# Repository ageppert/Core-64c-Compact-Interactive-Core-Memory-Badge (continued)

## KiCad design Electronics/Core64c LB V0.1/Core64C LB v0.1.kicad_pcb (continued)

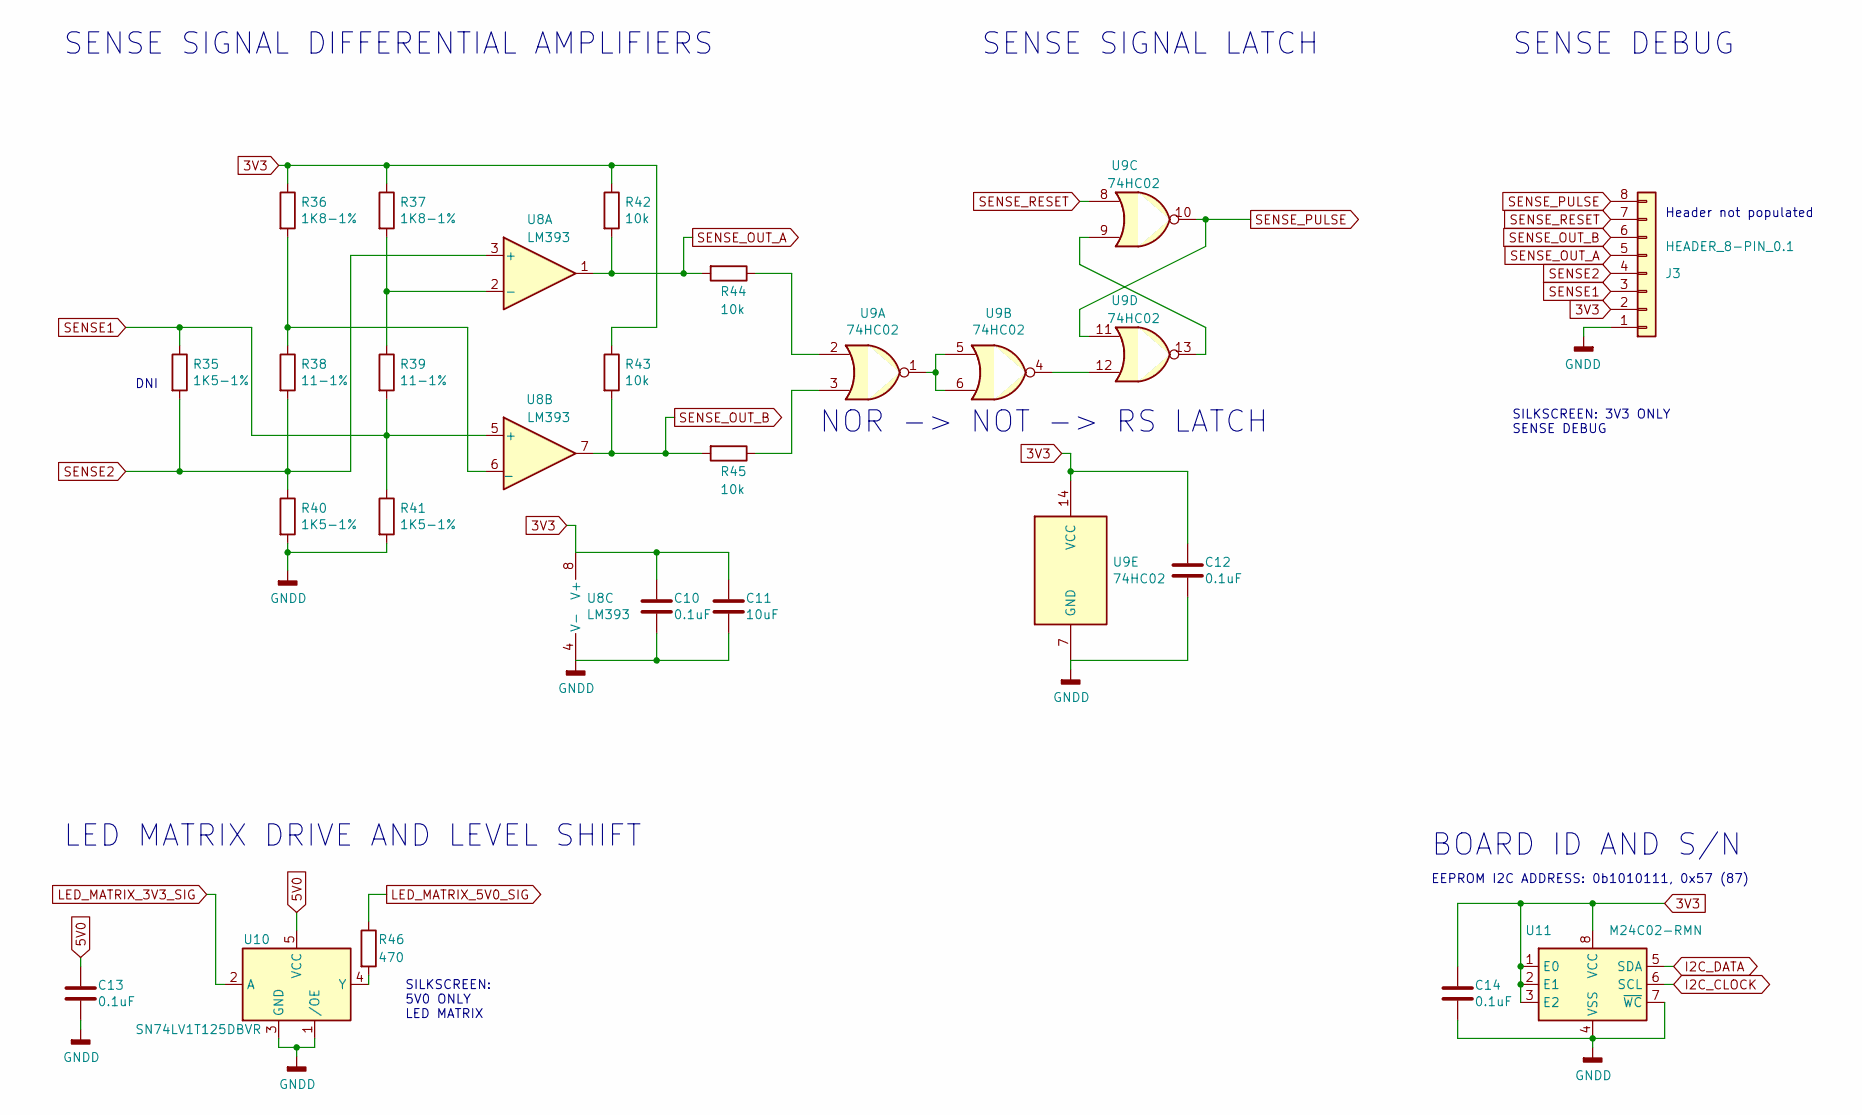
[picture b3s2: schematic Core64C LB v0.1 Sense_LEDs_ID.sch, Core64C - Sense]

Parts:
C10, C12, C13, C14: 0.1uF; C_0805_2012Metric
C11: 10uF; C_0805_2012Metric
J3: HEADER_8-PIN_0.1; PinSocket_1x08_P2.54mm_Vertical
R35, R40, R41: 1K5-1%; R_0805_2012Metric
R36, R37: 1K8-1%; R_0805_2012Metric
R38, R39: 11-1%; R_0805_2012Metric
R42, R43, R44, R45: 10k; R_0805_2012Metric
R46: 470; R_0805_2012Metric
U3, U8: LM393; SOIC-8_W3.9mm
U9: 74HC02; SOIC-14_3.9x8.7mm_P1.27mm
U10: SN74LV1T125DBVR; SOT-23-5; LCSC C473338
U11: M24C02-RMN; SOIC-8_3.9x4.9mm_P1.27mm

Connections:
3V3: C10.1, C11.1, C12.1, C14.1, J3.2, R36.1, R37.1, R42.1, R43.1, U8.8 (V+), U9.14 (VCC), U11.1 (E0), U11.2 (E1), U11.3 (E2), U11.8 (VCC); also elsewhere on the board
5V0: C13.1, U10.5 (VCC); also elsewhere on the board
-BATT: C10.2, C11.2, C12.2, C13.2, C14.2, J3.1, R40.2, R41.2, U8.4 (V-), U9.7 (GND), U10.1 (/OE), U10.3 (GND), U11.4 (VSS), U11.7 (~WC); also elsewhere on the board
I2C_CLOCK: U11.6 (SCL); also elsewhere on the board
I2C_DATA: U11.5 (SDA); also elsewhere on the board
LED_MATRIX_3V3_SIG: U10.2 (A); also elsewhere on the board
LED_MATRIX_5V0_SIG: R46.1; also elsewhere on the board
unnamed: R36.2, R38.1, U8.6 (_)
unnamed: R44.1, U9.2
unnamed: R45.1, U9.3
unnamed: R46.2, U10.4 (Y)
unnamed: U9.1, U9.5, U9.6
unnamed: U9.4, U9.12
unnamed: U9.9, U9.13
SENSE1: J3.3, R35.1, R39.2, R41.1, U8.5 (+); also elsewhere on the board
SENSE_OUT_B: J3.6, R43.2, R45.2, U8.7
SENSE_PULSE: J3.8, U9.10, U9.11; also elsewhere on the board
SENSE_RESET: J3.7, U9.8; also elsewhere on the board

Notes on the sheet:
SENSE SIGNAL DIFFERENTIAL AMPLIFIERS
DNI
SENSE SIGNAL LATCH
SENSE DEBUG
SILKSCREEN: 3V3 ONLY SENSE DEBUG
NOR -> NOT -> RS LATCH
LED MATRIX DRIVE AND LEVEL SHIFT
SILKSCREEN: 5V0 ONLY LED MATRIX
BOARD ID AND S/N
EEPROM I2C ADDRESS: 0b1010111, 0x57 (87)
Header not populated

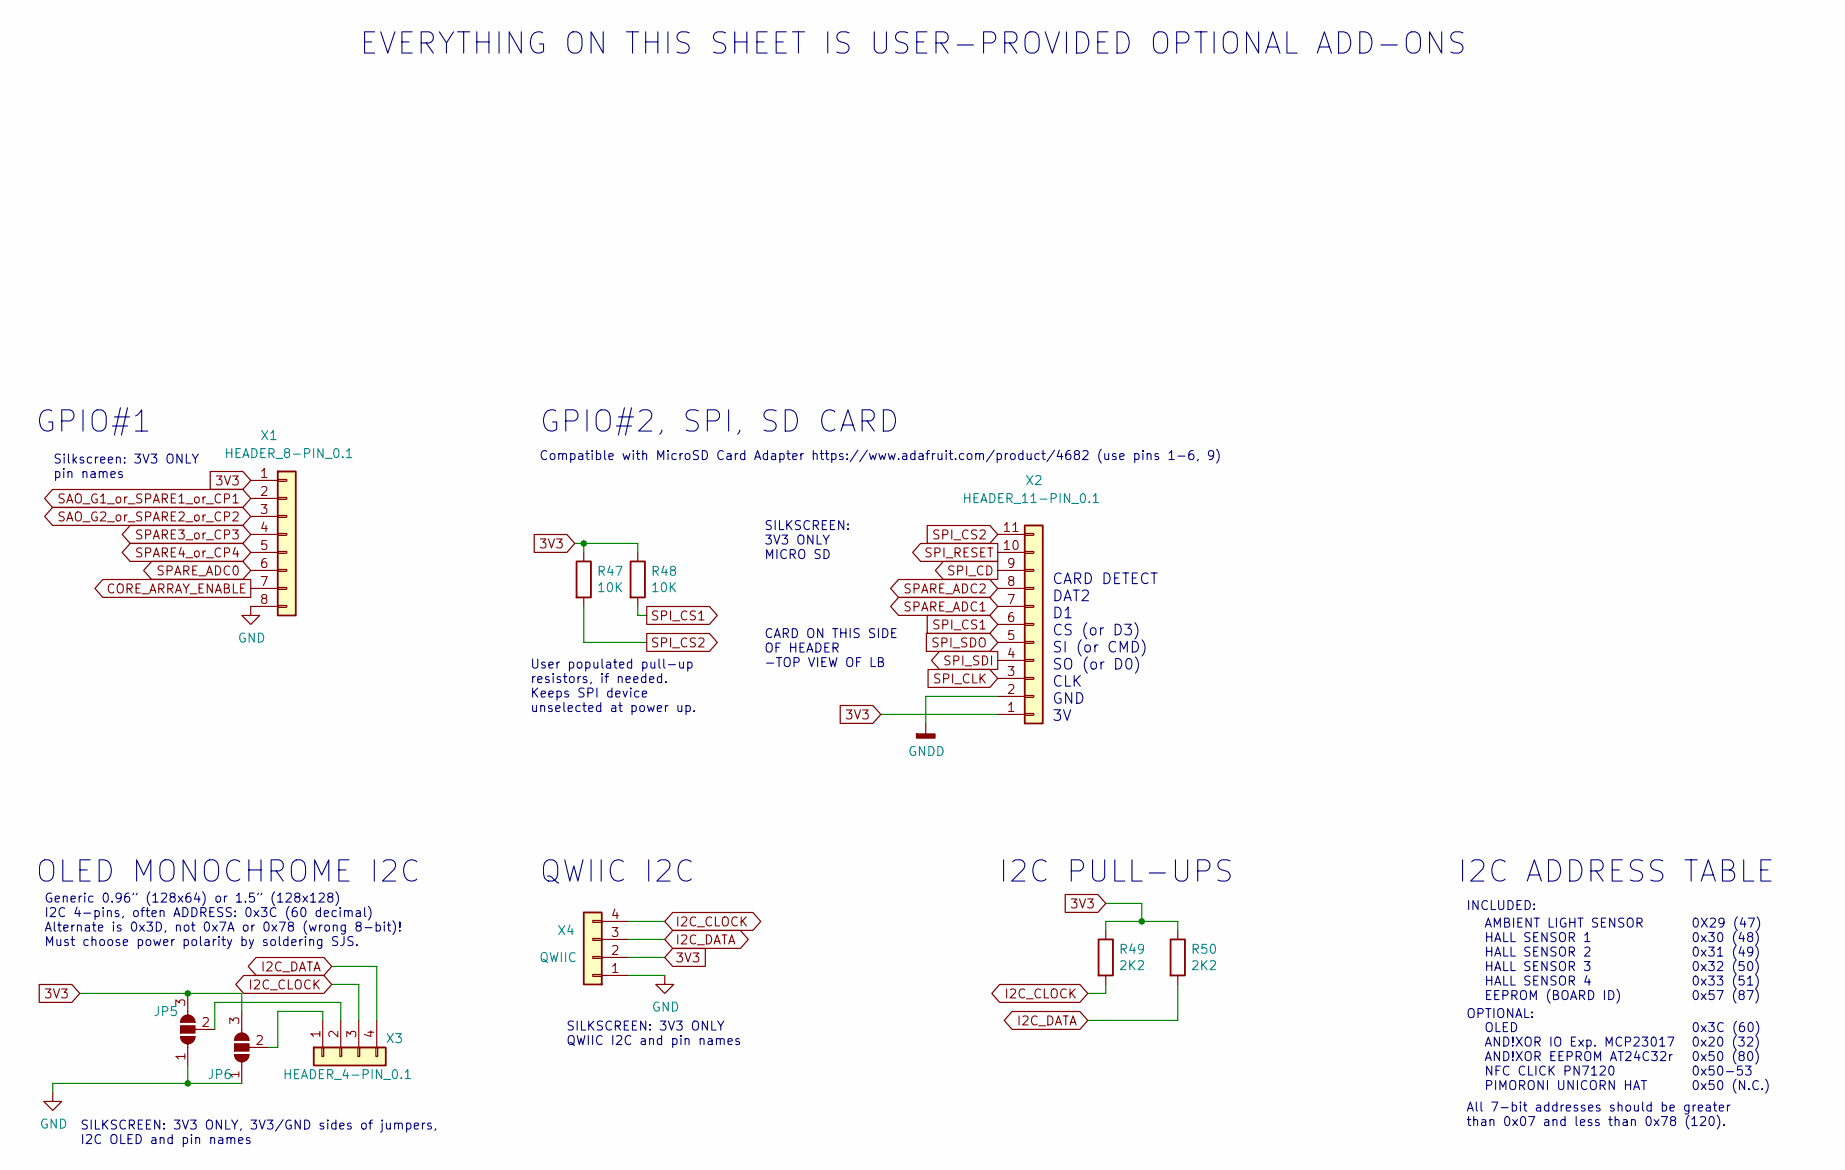
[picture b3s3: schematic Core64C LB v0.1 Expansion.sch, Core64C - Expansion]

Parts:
JP5, JP6: SolderJumper_3_Open; SolderJumper-3_P1.3mm_Open_Pad1.0x1.5mm_NumberLabels
R47, R48: 10K; R_0805_2012Metric
R49, R50: 2K2; R_0805_2012Metric
X1: HEADER_8-PIN_0.1; PinSocket_1x08_P2.54mm_Vertical
X2: HEADER_11-PIN_0.1; PinSocket_1x11_P2.54mm_Vertical
X3: HEADER_4-PIN_0.1; PinSocket_1x04_P2.54mm_Vertical
X4: QWIIC; JST_SH_SM04B-SRSS-TB_1x04-1MP_P1.00mm_Horizontal

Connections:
3V3: JP5.3 (B), JP6.3 (B), R47.1, R48.1, R49.1, R50.1, X1.1, X2.1, X4.2; also elsewhere on the board
3V3_MON: X2.7; also elsewhere on the board
-BATT: JP5.1 (A), JP6.1 (A), X1.8, X2.2, X4.1; also elsewhere on the board
BAT_MON: X1.6; also elsewhere on the board
CORE_ARRAY_ENABLE: X1.7; also elsewhere on the board
CP1_EN: X1.2; also elsewhere on the board
CP2_EN: X1.3; also elsewhere on the board
CP3_EN: X1.4, X2.9; also elsewhere on the board
CP4_EN: X1.5, X2.10; also elsewhere on the board
HS1: X2.4; also elsewhere on the board
HS2: R48.2, X2.6; also elsewhere on the board
HS3: X2.3; also elsewhere on the board
HS4: X2.5; also elsewhere on the board
I2C_CLOCK: R49.2, X3.3, X4.4; also elsewhere on the board
I2C_DATA: R50.2, X3.4, X4.3; also elsewhere on the board
LED_MATRIX_3V3_SIG: R47.2, X2.11; also elsewhere on the board
unnamed: JP5.2 (C), X3.2
unnamed: JP6.2 (C), X3.1
SPARE_ADC2: X2.8; also elsewhere on the board

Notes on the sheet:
OLED MONOCHROME I2C
Generic 0.96” (128x64) or 1.5” (128x128) I2C 4-pins, often ADDRESS: 0x3C (60 decimal) Alternate is 0x3D, not 0x7A or 0x78 (wrong 8-bit)! Must choose power polarity by soldering SJS.
QWIIC I2C
SILKSCREEN: 3V3 ONLY, 3V3/GND sides of jumpers, I2C OLED and pin names
Silkscreen: 3V3 ONLY pin names
GPIO#1
EVERYTHING ON THIS SHEET IS USER-PROVIDED OPTIONAL ADD-ONS
SILKSCREEN: 3V3 ONLY QWIIC I2C and pin names
All 7-bit addresses should be greater than 0x07 and less than 0x78 (120).
AMBIENT LIGHT SENSOR HALL SENSOR 1 HALL SENSOR 2 HALL SENSOR 3 HALL SENSOR 4 EEPROM (BOARD ID)
0X29 (47) 0x30 (48) 0x31 (49) 0x32 (50) 0x33 (51) 0x57 (87)
INCLUDED:
OPTIONAL:
OLED AND!XOR IO Exp. MCP23017 AND!XOR EEPROM AT24C32r NFC CLICK PN7120 PIMORONI UNICORN HAT
0x3C (60) 0x20 (32) 0x50 (80) 0x50-53 0x50 (N.C.)
I2C ADDRESS TABLE
I2C PULL-UPS
GPIO#2, SPI, SD CARD
Compatible with MicroSD Card Adapter https://www.adafruit.com/product/4682 (use pins 1-6, 9)
SILKSCREEN: 3V3 ONLY MICRO SD
CARD ON THIS SIDE OF HEADER -TOP VIEW OF LB
CARD DETECT DAT2 D1 CS (or D3) SI (or CMD) SO (or D0) CLK GND 3V
User populated pull-up resistors, if needed. Keeps SPI device unselected at power up.

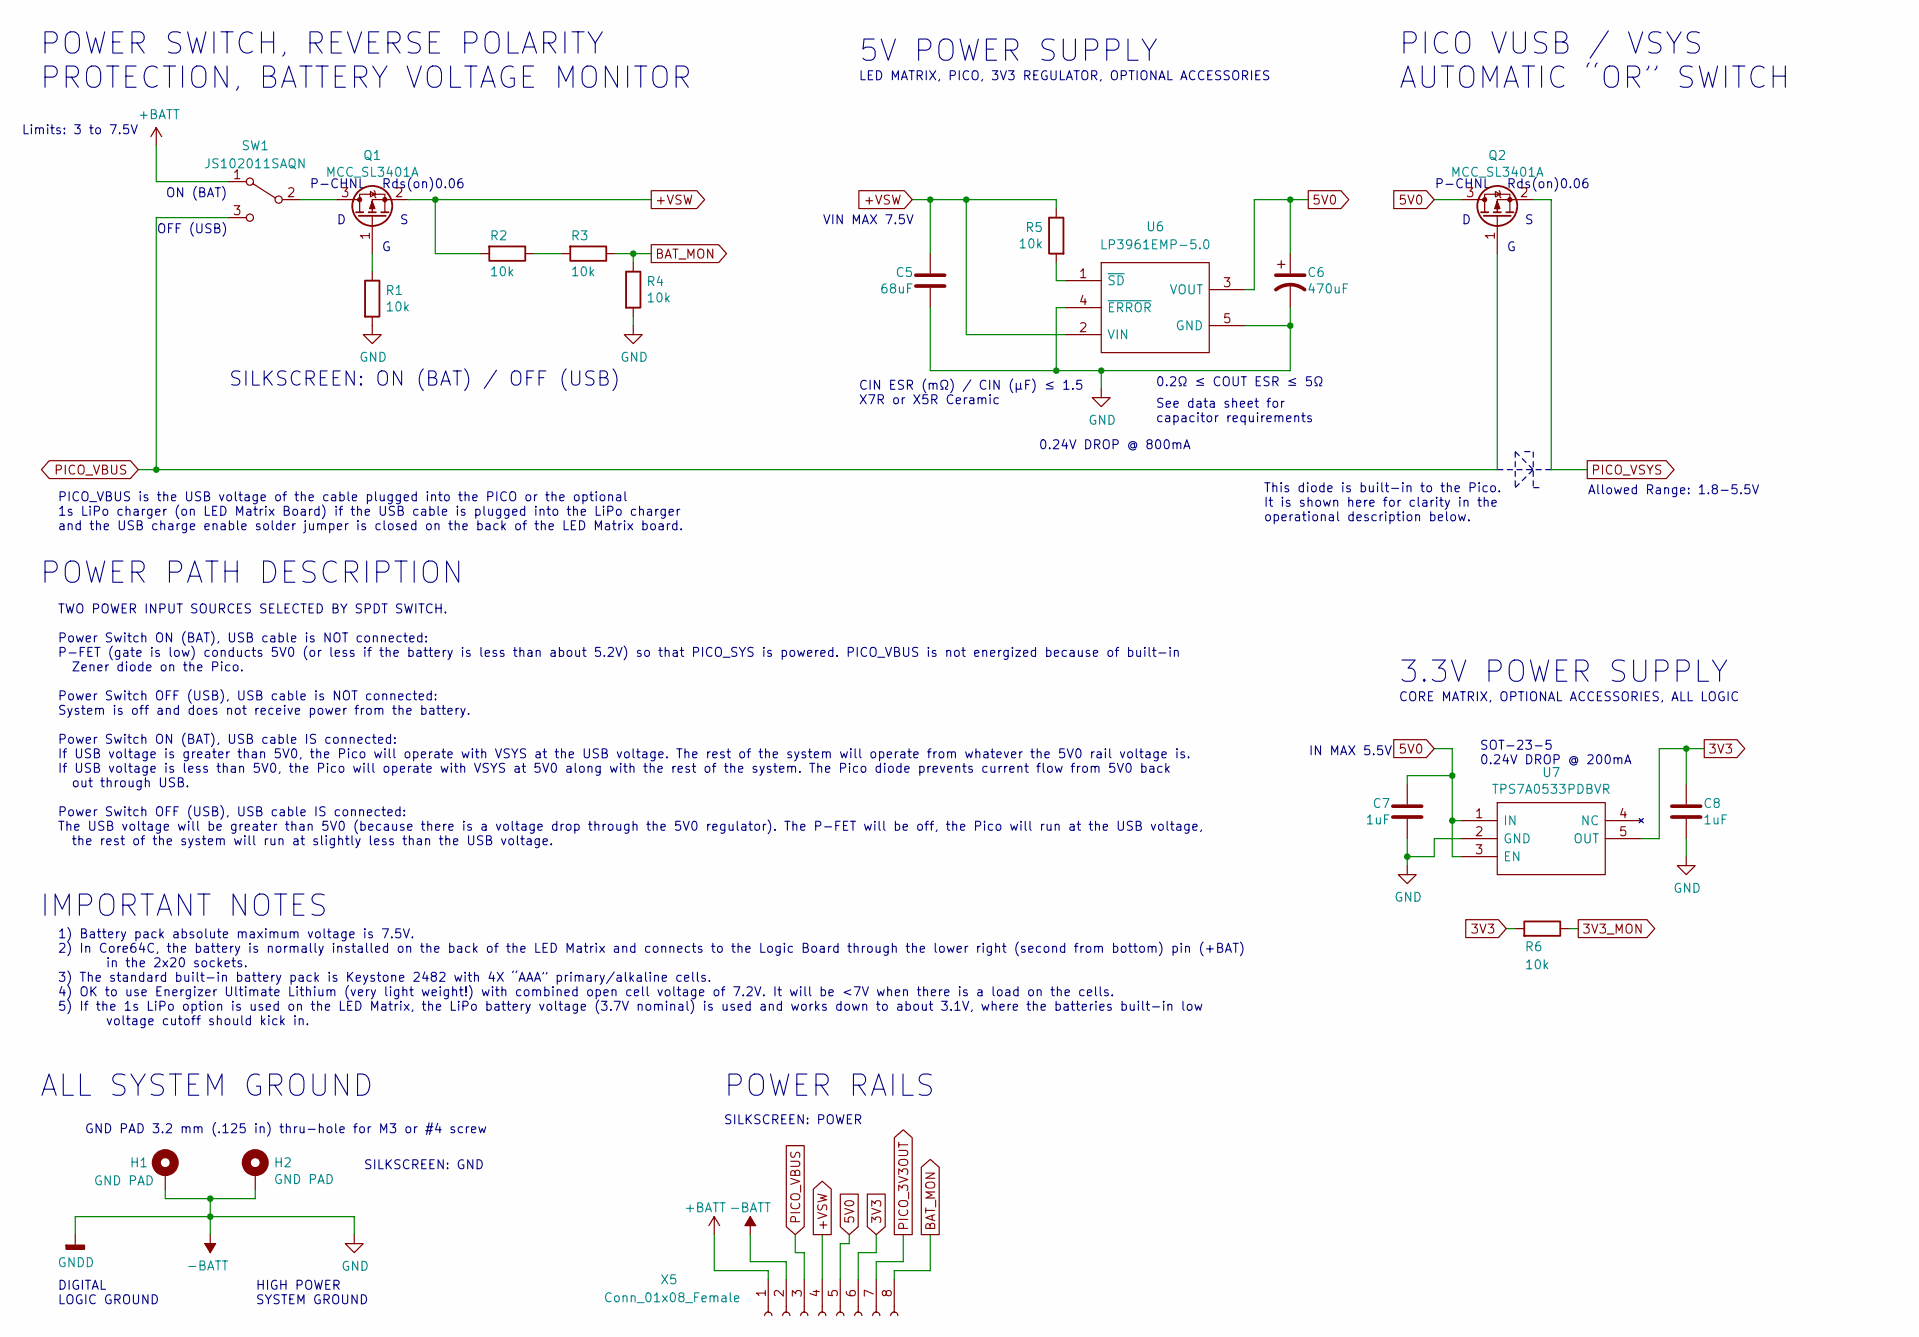
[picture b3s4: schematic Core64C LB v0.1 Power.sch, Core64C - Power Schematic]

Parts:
C5: 68uF; C_1206_3216Metric
C6: 470uF; CP_Elec_6.3x7.7; Digi-Key_PN 565-EMHL100ARA471MHA0GCT-ND
C7, C8: 1uF; C_0805_2012Metric
H1, H2: GND PAD; MountingHole_3.2mm_M3_Pad_Via
Q1, Q2: MCC_SL3401A; SOT-23-3; LCSC C350311
R1, R2, R3, R4, R5, R6: 10k; R_0805_2012Metric
SW1: JS102011SAQN; SW_SPDT_CK-JS102011SAQN_Core64_Recessed
U6: LP3961EMP-5.0; SOT150P696X180-5N; Manufacturer_Part_Number LP3961EMP-5.0; Mouser Part Number 926-LP3961EMP-50
U7: TPS7A0533PDBVR; SOT95P280X145-5N; Manufacturer_Part_Number TPS7A0533PDBVR; Mouser Part Number 595-TPS7A0533PDBVR
X5: Conn_01x08_Female; PinSocket_1x08_P2.54mm_Vertical

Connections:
3V3: C8.1, R6.2, U7.5 (OUT), X5.6; also elsewhere on the board
3V3_MON: R6.1; also elsewhere on the board
5V0: C6.1, C7.1, Q2.3 (D), U6.3 (VOUT), U7.1 (IN), U7.3 (EN), X5.5; also elsewhere on the board
+BATT: SW1.1 (A), X5.1; also elsewhere on the board
+VSW: C5.1, Q1.2 (S), R2.2, R5.1, U6.2 (VIN), X5.4
-BATT: C5.2, C6.2, C7.2, C8.2, H1.1, H2.1, R1.2, R4.2, U6.4 (~ERROR), U6.5 (GND), U7.2 (GND), X5.2; also elsewhere on the board
BAT_MON: R3.1, R4.1, X5.8; also elsewhere on the board
unnamed: Q1.1 (G), R1.1
unnamed: Q1.3 (D), SW1.2 (B)
unnamed: R2.1, R3.2
unnamed: R5.2, U6.1 (~SD)
PICO_3V3OUT: X5.7; also elsewhere on the board
PICO_VBUS: Q2.1 (G), SW1.3 (C), X5.3; also elsewhere on the board
PICO_VSYS: Q2.2 (S); also elsewhere on the board

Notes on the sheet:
CORE MATRIX, OPTIONAL ACCESSORIES, ALL LOGIC
POWER SWITCH, REVERSE POLARITY PROTECTION, BATTERY VOLTAGE MONITOR
3.3V POWER SUPPLY
LED MATRIX, PICO, 3V3 REGULATOR, OPTIONAL ACCESSORIES
ALL SYSTEM GROUND
POWER RAILS
HIGH POWER SYSTEM GROUND
DIGITAL LOGIC GROUND
SILKSCREEN: ON (BAT) / OFF (USB)
5V POWER SUPPLY
P-CHNL
SOT-23-5 0.24V DROP @ 200mA
CIN ESR (mΩ) / CIN (μF) ≤ 1.5 X7R or X5R Ceramic
0.2Ω ≤ COUT ESR ≤ 5Ω
See data sheet for capacitor requirements
GND PAD 3.2 mm (.125 in) thru-hole for M3 or #4 screw
SILKSCREEN: GND
SILKSCREEN: POWER
ON (BAT)
OFF (USB)
Rds(on)0.06
VIN MAX 7.5V
0.24V DROP @ 800mA
IN MAX 5.5V
Allowed Range: 1.8-5.5V
TWO POWER INPUT SOURCES SELECTED BY SPDT SWITCH. Power Switch ON (BAT), USB cable is NOT connected: P-FET (gate is low) conducts 5V0 (or less if the battery is less than about 5.2V) so that PICO_SYS is powered. PICO_VBUS is not energized because of built-in Zener diode on the Pico. Power Switch OFF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
PICO VUSB / VSYS AUTOMATIC “OR” SWITCH
This diode is built-in to the Pico. It is shown here for clarity in the operational description below.
PICO_VBUS is the USB voltage of the cable plugged into the PICO or the optional 1s LiPo charger (on LED Matrix Board) if the USB cable is plugged into the LiPo charger and the USB charge enable solder jumper is closed on the back of the LED Matrix board.
POWER PATH DESCRIPTION
1) Battery pack absolute maximum voltage is 7.5V. 2) In Core64C, the battery is normally installed on the back of the LED Matrix and connects to the Logic Board through the lower right (second from bottom) pin (+BAT) in the 2x20 sockets. 3) The standard built-in battery pack is Keystone 2482 with 4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
IMPORTANT NOTES
Limits: 3 to 7.5V

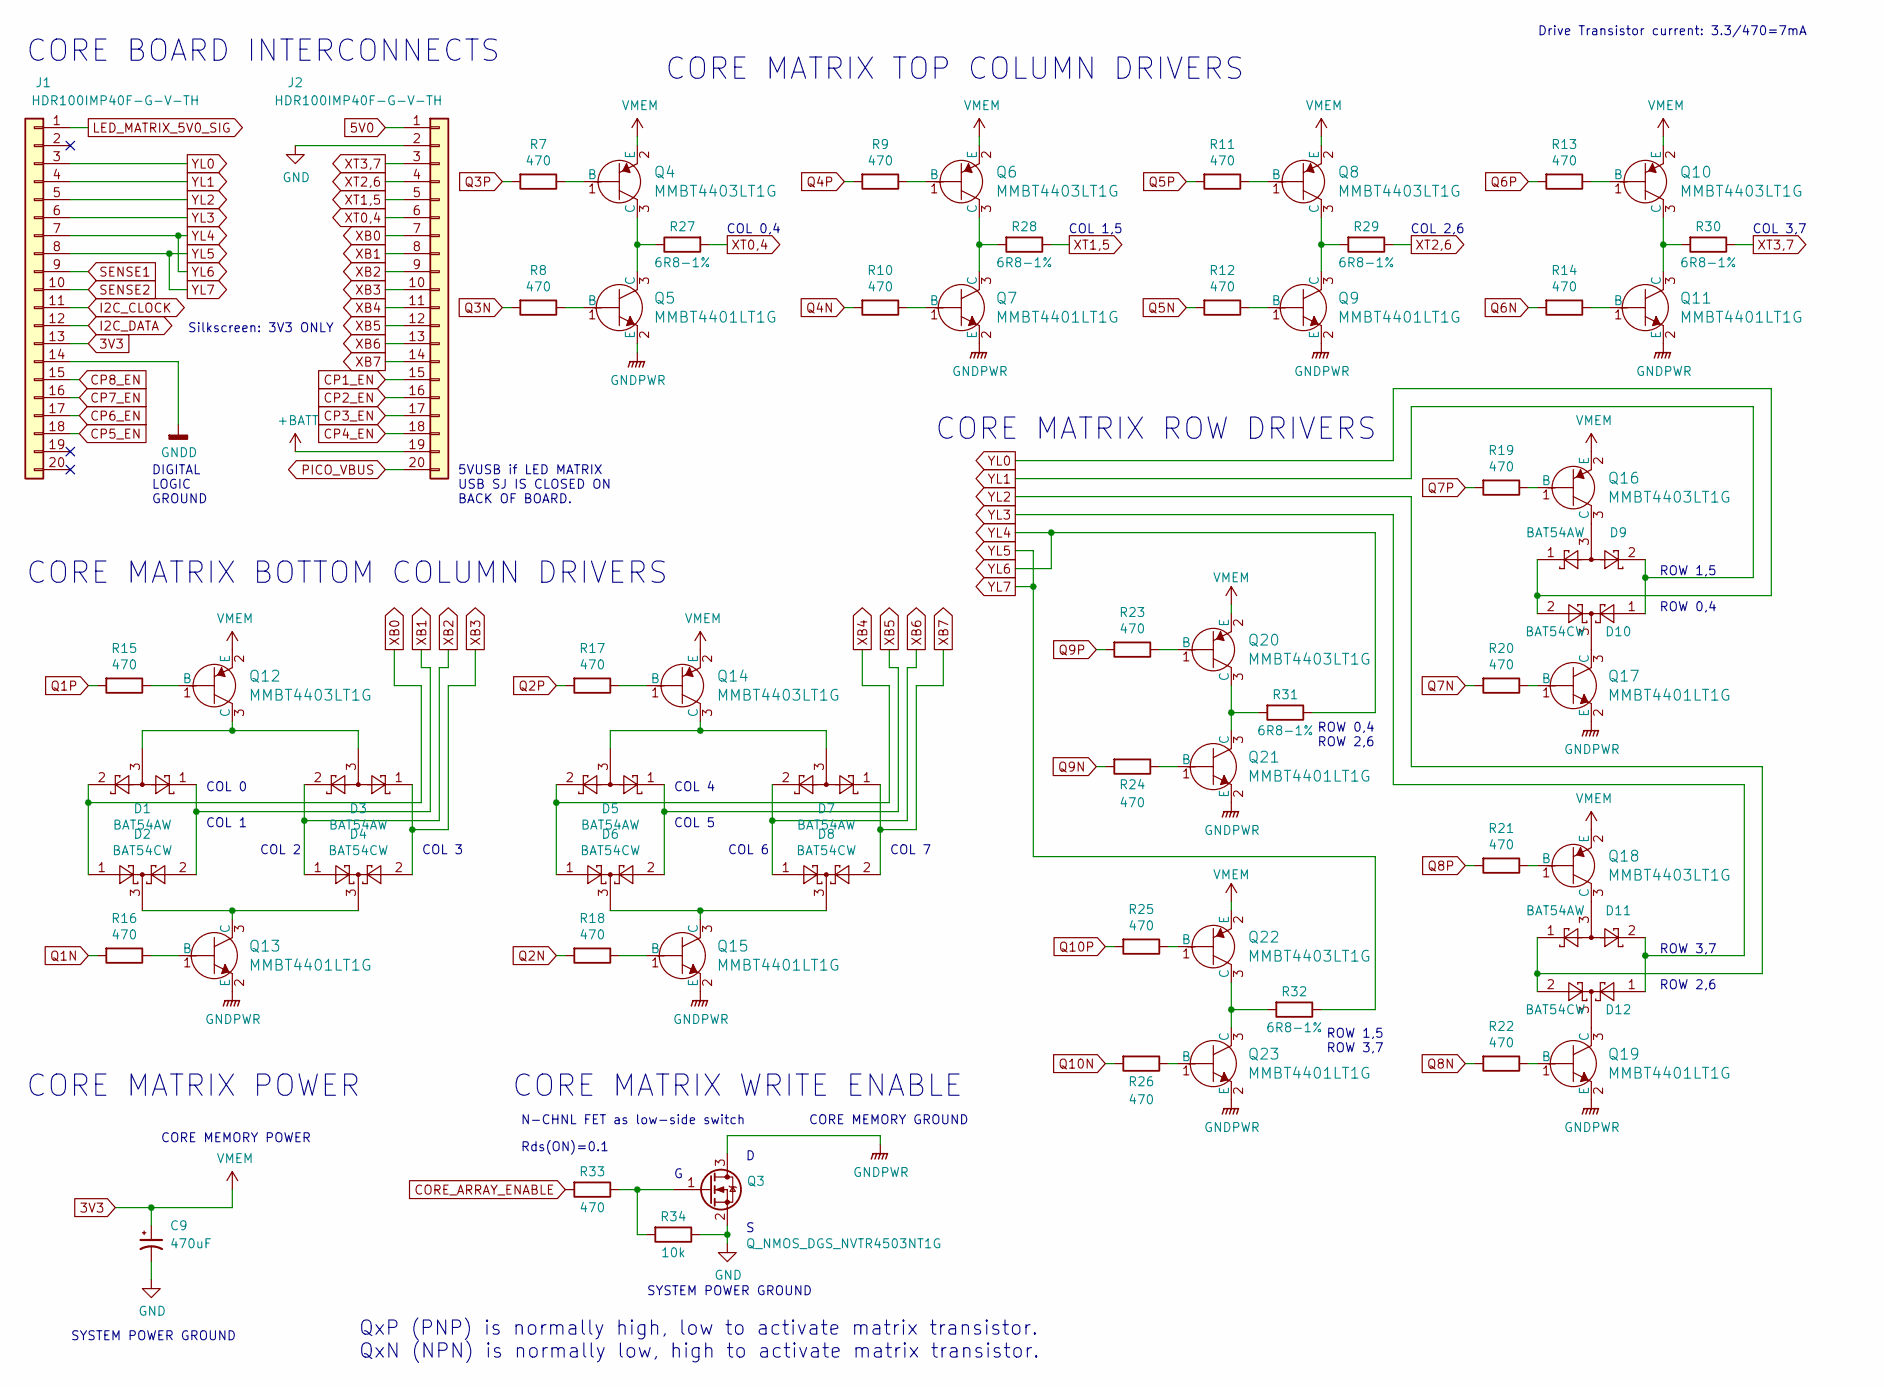
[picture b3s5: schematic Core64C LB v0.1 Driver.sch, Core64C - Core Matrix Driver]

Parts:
C9: 470uF; CP_Elec_6.3x7.7; Digi-Key_PN 565-EMHL100ARA471MHA0GCT-ND
D1, D3, D5, D7, D9, D11: BAT54AW; SOT-323_SC-70
D2, D4, D6, D8, D10, D12: BAT54CW; SOT-323_SC-70
J1, J2: HDR100IMP40F-G-V-TH; PinSocket_1x20_P2.54mm_Vertical
Q3: Q_NMOS_DGS_NVTR4503NT1G; SOT-23-3; LCSC C184182
Q4, Q6, Q8, Q10, Q12, Q14, Q16, Q18, Q20, Q22: MMBT4403LT1G; SOT-23-3; MPN MMBT4403LT1G; Digi-Key_PN MMBT4403LT1GOSCT-ND
Q5, Q7, Q9, Q11, Q13, Q15, Q17, Q19, Q21, Q23: MMBT4401LT1G; SOT-23-3; MPN MMBT4401LT1G; Digi-Key_PN MMBT4401LT1GOSCT-ND
R7, R8, R9, R10, R11, R12, R13, R14, R15, R16, R17, R18, R19, R20, R21, R22, R23, R24, R25, R26, R33: 470; R_0805_2012Metric
R27, R28, R29, R30, R31, R32: 6R8-1%; R_0805_2012Metric
R34: 10k; R_0805_2012Metric

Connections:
3V3: C9.1, J1.13, Q4.2 (E), Q6.2 (E), Q8.2 (E), Q10.2 (E), Q12.2 (E), Q14.2 (E), Q16.2 (E), Q18.2 (E), Q20.2 (E), Q22.2 (E); also elsewhere on the board
5V0: J2.1; also elsewhere on the board
+BATT: J2.19; also elsewhere on the board
-BATT: C9.2, J1.14, J2.2, Q3.2 (S), R34.1; also elsewhere on the board
CORE_ARRAY_ENABLE: R33.2; also elsewhere on the board
CP1_EN: J2.15; also elsewhere on the board
CP2_EN: J2.16; also elsewhere on the board
CP3_EN: J2.17; also elsewhere on the board
CP4_EN: J2.18; also elsewhere on the board
CP5_EN: J1.18; also elsewhere on the board
CP6_EN: J1.17; also elsewhere on the board
CP7_EN: J1.16; also elsewhere on the board
CP8_EN: J1.15; also elsewhere on the board
GNDPWR: Q3.3 (D), Q5.2 (E), Q7.2 (E), Q9.2 (E), Q11.2 (E), Q13.2 (E), Q15.2 (E), Q17.2 (E), Q19.2 (E), Q21.2 (E), Q23.2 (E)
I2C_CLOCK: J1.11; also elsewhere on the board
I2C_DATA: J1.12; also elsewhere on the board
LED_MATRIX_5V0_SIG: J1.1; also elsewhere on the board
unnamed: D1.3, D3.3, Q12.3 (C)
unnamed: D2.3, D4.3, Q13.3 (C)
unnamed: D5.3, D7.3, Q14.3 (C)
unnamed: D6.3, D8.3, Q15.3 (C)
unnamed: D9.3, Q16.3 (C)
unnamed: D10.3, Q17.3 (C)
unnamed: D11.3, Q18.3 (C)
unnamed: D12.3, Q19.3 (C)
unnamed: Q3.1 (G), R33.1, R34.2
unnamed: Q4.1 (B), R7.1
unnamed: Q4.3 (C), Q5.3 (C), R27.1
unnamed: Q5.1 (B), R8.1
unnamed: Q6.1 (B), R9.1
unnamed: Q6.3 (C), Q7.3 (C), R28.2
unnamed: Q7.1 (B), R10.1
unnamed: Q8.1 (B), R11.1
unnamed: Q8.3 (C), Q9.3 (C), R29.2
unnamed: Q9.1 (B), R12.1
unnamed: Q10.1 (B), R13.1
unnamed: Q10.3 (C), Q11.3 (C), R30.2
unnamed: Q11.1 (B), R14.1
unnamed: Q12.1 (B), R15.1
unnamed: Q13.1 (B), R16.1
unnamed: Q14.1 (B), R17.1
unnamed: Q15.1 (B), R18.1
unnamed: Q16.1 (B), R19.1
unnamed: Q17.1 (B), R20.1
unnamed: Q18.1 (B), R21.1
unnamed: Q19.1 (B), R22.1
unnamed: Q20.1 (B), R23.1
unnamed: Q20.3 (C), Q21.3 (C), R31.2
unnamed: Q21.1 (B), R24.1
unnamed: Q22.1 (B), R25.1
unnamed: Q22.3 (C), Q23.3 (C), R32.2
unnamed: Q23.1 (B), R26.1
PICO_VBUS: J2.20; also elsewhere on the board
Q1N: R16.2; also elsewhere on the board
Q1P: R15.2; also elsewhere on the board
Q2N: R18.2; also elsewhere on the board
Q2P: R17.2; also elsewhere on the board
Q3N: R8.2; also elsewhere on the board
Q3P: R7.2; also elsewhere on the board
Q4N: R10.2; also elsewhere on the board
Q4P: R9.2; also elsewhere on the board
Q5N: R12.2; also elsewhere on the board
Q5P: R11.2; also elsewhere on the board
Q6N: R14.2; also elsewhere on the board
Q6P: R13.2; also elsewhere on the board
Q7N: R20.2; also elsewhere on the board
Q7P: R19.2; also elsewhere on the board
Q8N: R22.2; also elsewhere on the board
Q8P: R21.2; also elsewhere on the board
Q9N: R24.2; also elsewhere on the board
Q9P: R23.2; also elsewhere on the board
Q10N: R26.2; also elsewhere on the board
Q10P: R25.2; also elsewhere on the board
SENSE1: J1.9; also elsewhere on the board
XB0: D1.2, D2.1, J2.7
XB1: D1.1, D2.2, J2.8
XB2: D3.2, D4.1, J2.9
XB3: D3.1, D4.2, J2.10
XB4: D5.2, D6.1, J2.11
XB5: D5.1, D6.2, J2.12
XB6: D7.2, D8.1, J2.13
XB7: D7.1, D8.2, J2.14
XT0,4: J2.6, R27.2
XT1,5: J2.5, R28.1
XT2,6: J2.4, R29.1
XT3,7: J2.3, R30.1
YL0: D9.1, D10.2, J1.3
YL1: D9.2, D10.1, J1.4
YL2: D11.1, D12.2, J1.5
YL3: D11.2, D12.1, J1.6
YL4: J1.7, R31.1
YL5: J1.8, R32.1

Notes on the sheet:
COL 0,4
COL 1,5
COL 2,6
COL 0
COL 1
COL 2
COL 3
COL 4
COL 5
COL 6
COL 7
ROW 0,4 ROW 2,6
ROW 1,5 ROW 3,7
ROW 0,4
ROW 3,7
ROW 1,5
ROW 2,6
CORE MEMORY GROUND
CORE MEMORY POWER
CORE MATRIX POWER
CORE MATRIX BOTTOM COLUMN DRIVERS
CORE MATRIX TOP COLUMN DRIVERS
CORE MATRIX ROW DRIVERS
CORE MATRIX WRITE ENABLE
DIGITAL LOGIC GROUND
SYSTEM POWER GROUND
CORE BOARD INTERCONNECTS
Silkscreen: 3V3 ONLY
QxP (PNP) is normally high, low to activate matrix transistor. QxN (NPN) is normally low, high to activate matrix transistor.
N-CHNL FET as low-side switch
Rds(ON)=0.1
Drive Transistor current: 3.3/470=7mA
5VUSB if LED MATRIX USB SJ IS CLOSED ON BACK OF BOARD.
COL 3,7

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
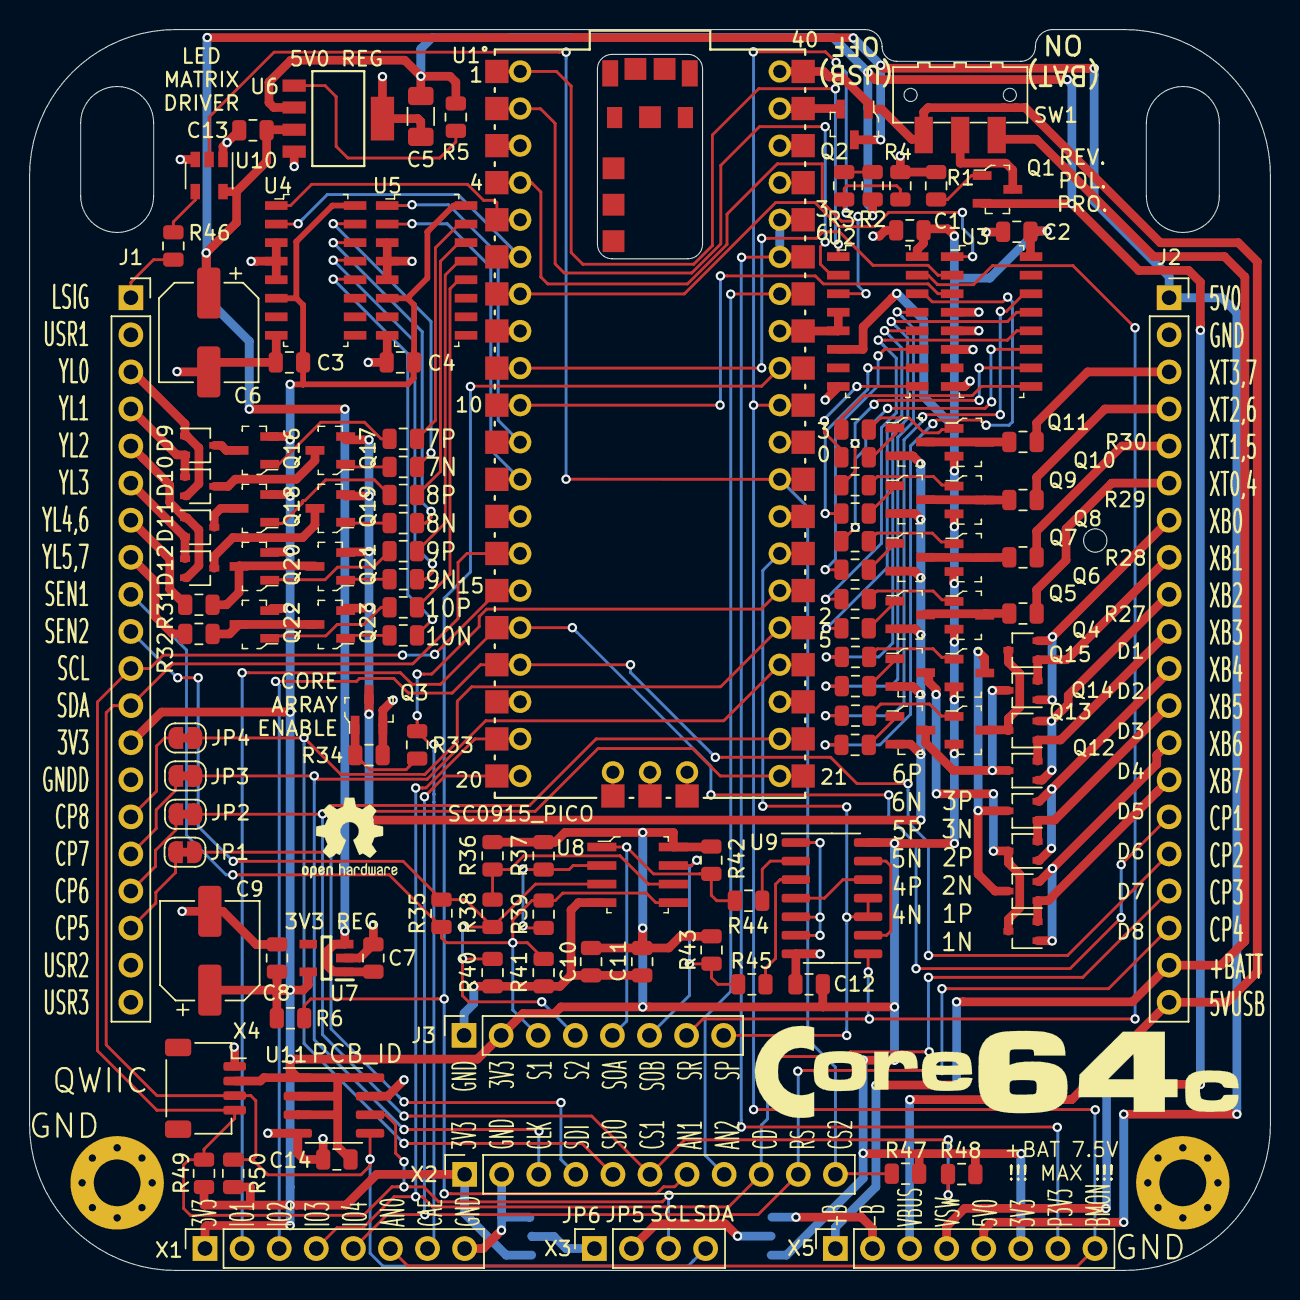
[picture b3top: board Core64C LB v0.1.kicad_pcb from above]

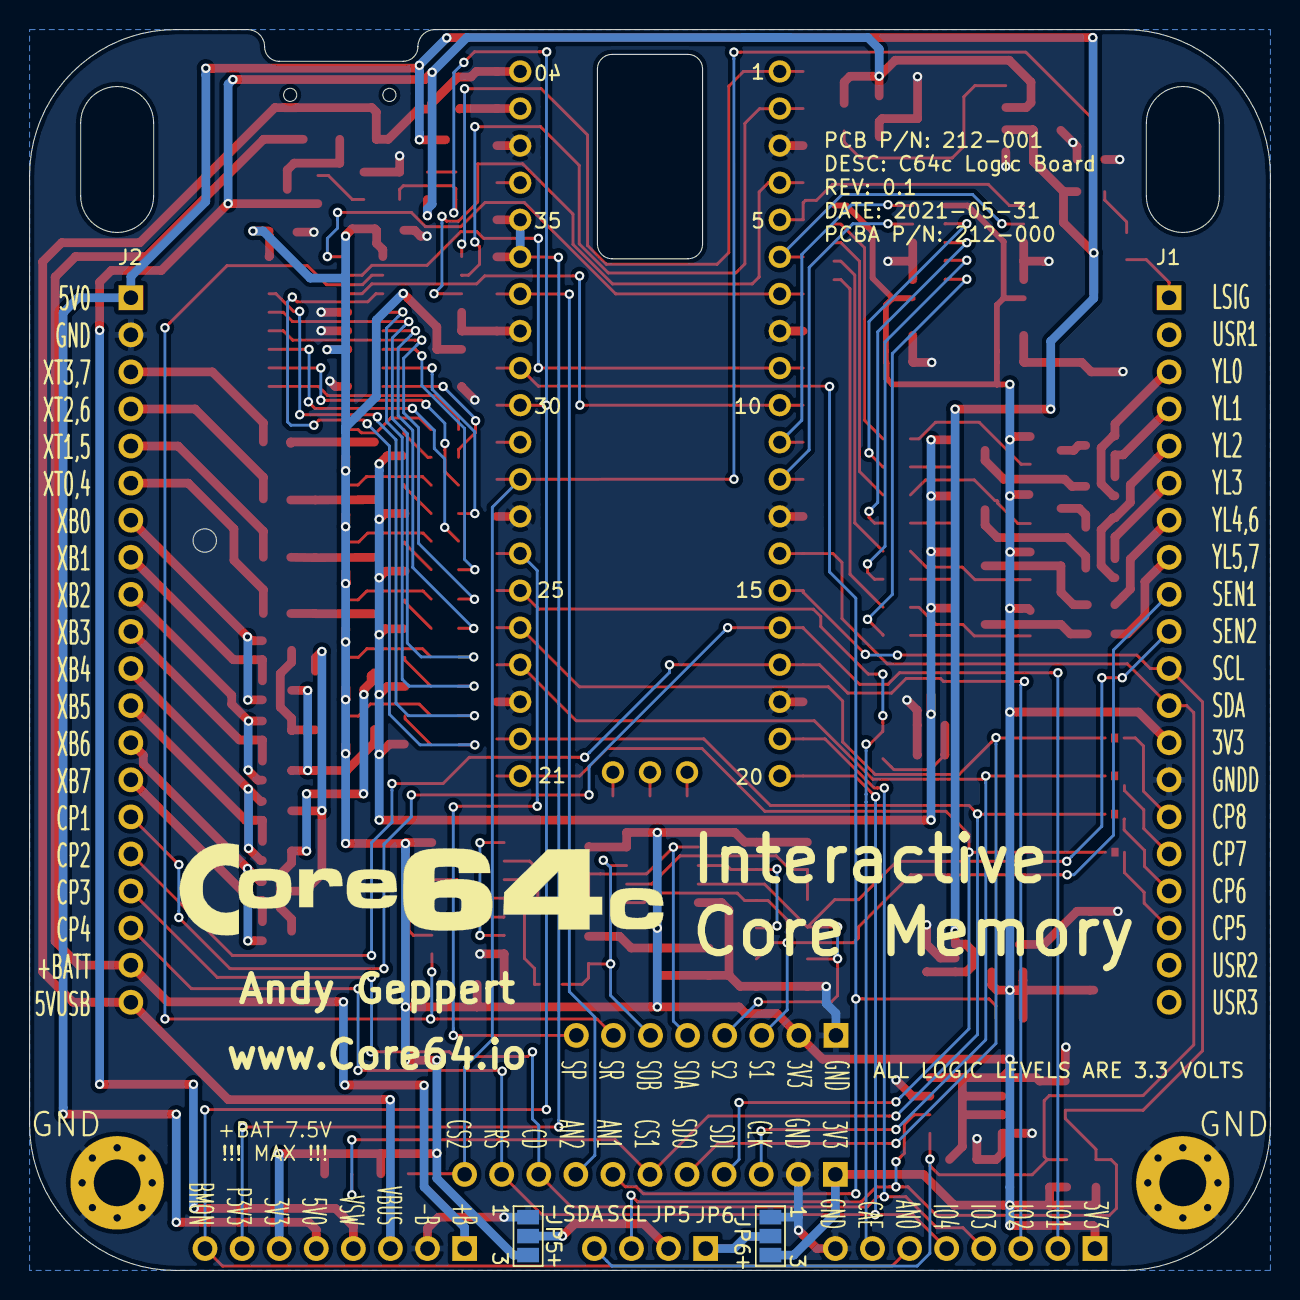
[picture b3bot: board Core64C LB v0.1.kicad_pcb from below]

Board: 2 copper layers, 85.0 x 85.0 mm, 130 parts (3 on the bottom side), 132 nets.

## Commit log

2021-09-26 Initial commit with Core64c Logic Board V0.2 and some sample test code
2022-05-18 HWV 0.3.0: Create and release Core64c Logic Board V0.3.0
    Correct shift register schematic, add TC0_MON as ADC3, move 5V0 cap down, alternate LDO v-regs with 0.1uF caps, rotate SPI GPIO 180°, matrix current setting resistors 6.8 Ohm, I2C pull-ups 1.2K, add 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
2022-05-20 HWV 0.3.0: Core64c Logic Board, add and rename data sheets, update BOM notes for JLCPCB component availability
2022-06-13 Correct Core64c LB v0.3 filename date from 2021 to 2022
2022-06-13 Create Core64c Logic Board v0.4 from v0.3.
    SCHEMATIC
    Remove 2x 10Ks between Comparators and NOR gate like Core64 V0.6 LB.
    Update Comparator output pull-ups to be 1K2 like Core64 V0.6 LB (and i2C pull-ups).
    Organize the Ref Des #s nicely, like Core64. D1-D12, Q1-Q20 in core matrix driver.
    COMPONENTS
    Find alternatives to get from LCSC, Matrix Drive FET
2024-10-10 Clean-up LB V0.4 design files
2024-10-10 Clean-up LB V0.5 files
2024-10-10 Add LB V0.6-V0.7 files
